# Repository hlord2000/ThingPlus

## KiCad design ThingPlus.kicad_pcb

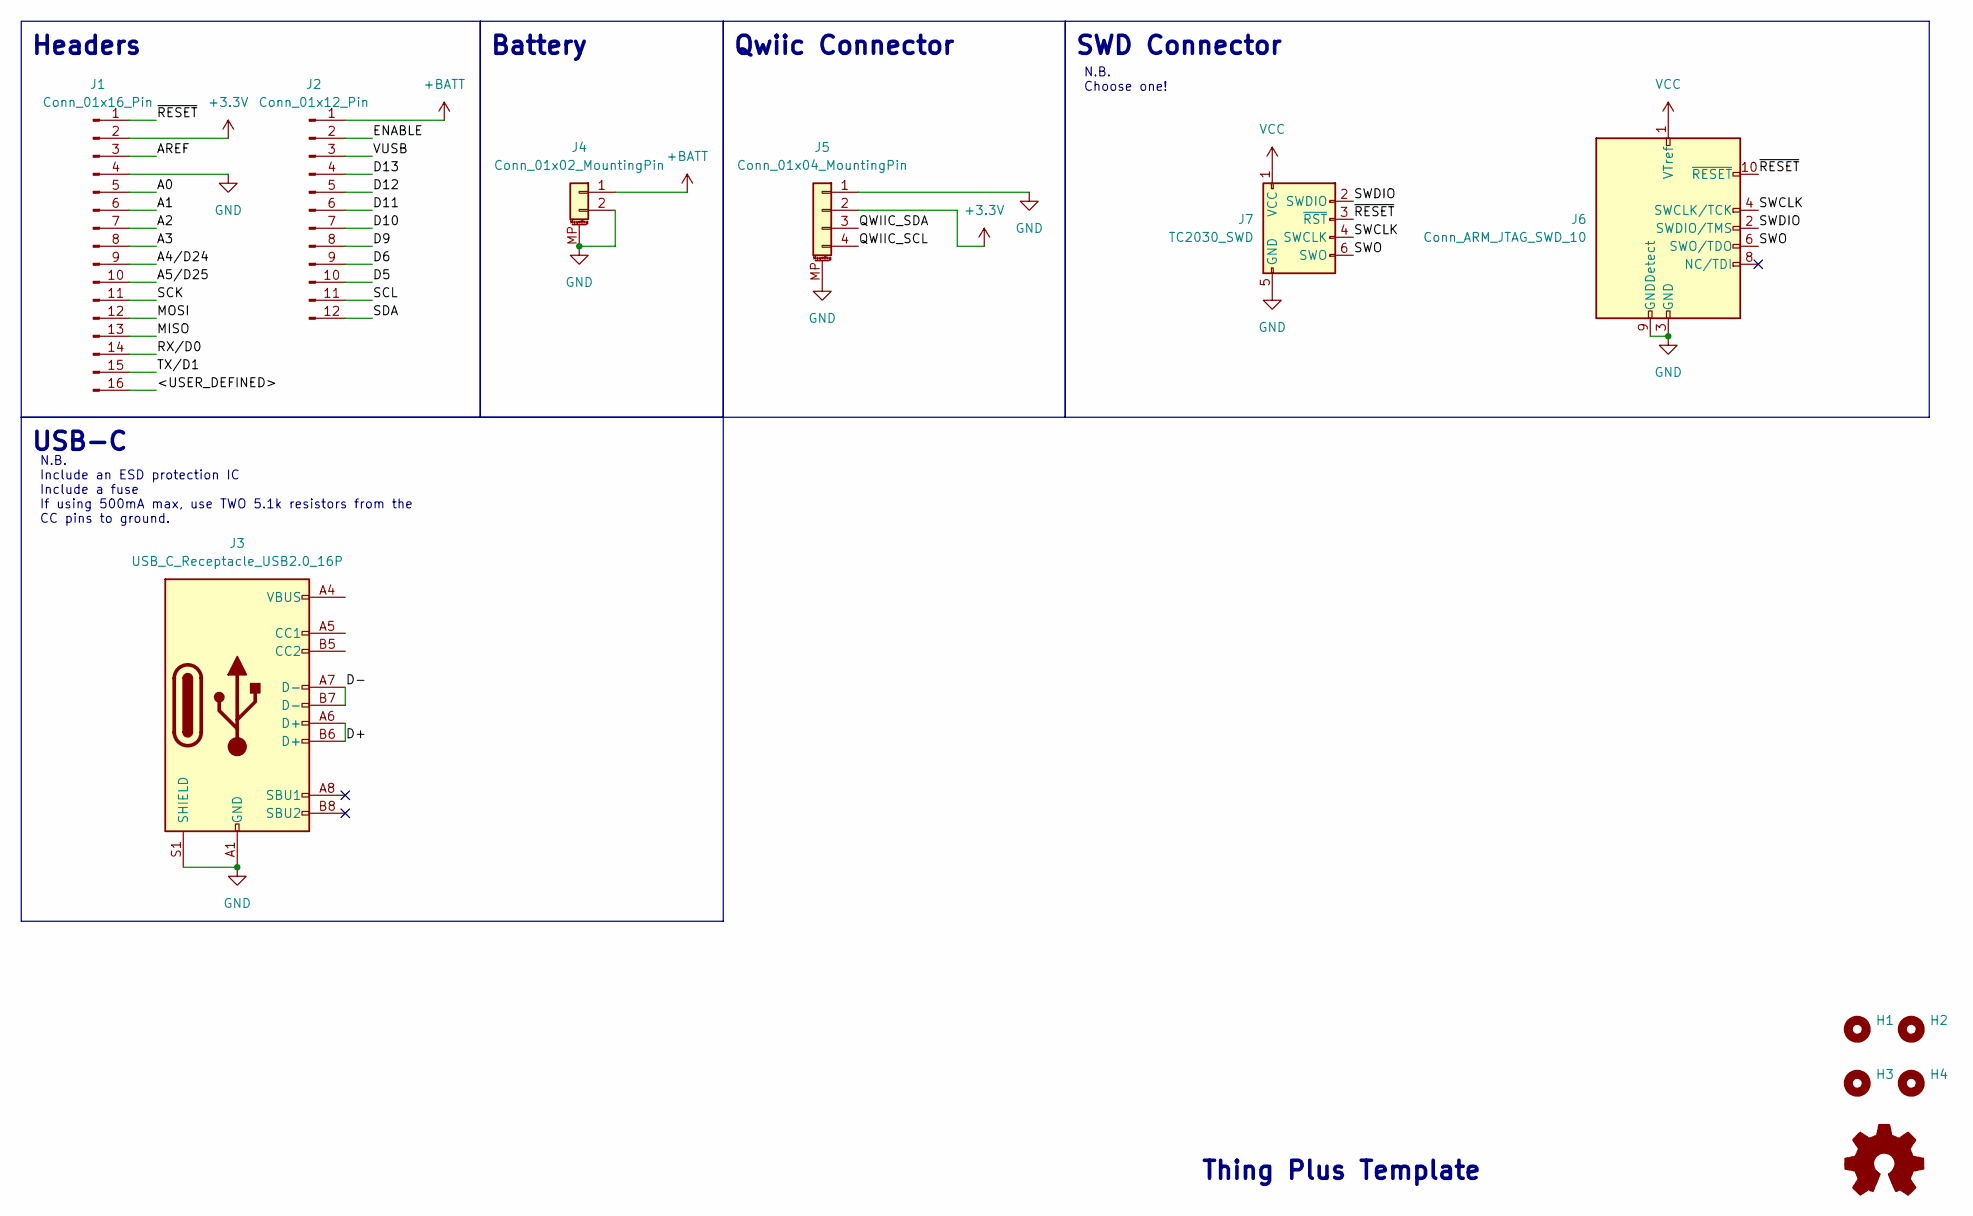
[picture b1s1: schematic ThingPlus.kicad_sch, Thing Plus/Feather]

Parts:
H1, H2, H3, H4: MountingHole; MountingHole_2.5mm
J1: Conn_01x16_Pin; PinHeader_1x16_P2.54mm_Vertical
J2: Conn_01x12_Pin; PinHeader_1x12_P2.54mm_Vertical
J3: USB_C_Receptacle_USB2.0_16P; USB_C_Receptacle_HRO_TYPE-C-31-M-12
J4: Conn_01x02_MountingPin; JST_PH_S2B-PH-SM4-TB_1x02-1MP_P2.00mm_Horizontal
J5: Conn_01x04_MountingPin; JST_SH_SM04B-SRSS-TB_1x04-1MP_P1.00mm_Horizontal
J6: Conn_ARM_JTAG_SWD_10; PinHeader_2x05_P1.27mm_Vertical_SMD
J7: TC2030_SWD; CON_TC2030_outlined

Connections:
+3.3V: J1.2, J5.2
+BATT: J2.1, J4.1
/<USER_DEFINED>: J1.16
/A0: J1.5
/A1: J1.6
/A2: J1.7
/A3: J1.8
/A4/D24: J1.9
/A5/D25: J1.10
/AREF: J1.3
/D5: J2.10
/D6: J2.9
/D9: J2.8
/D10: J2.7
/D11: J2.6
/D12: J2.5
/D13: J2.4
/D+: J3.A6 (D+), J3.B6 (D+)
/D-: J3.A7 (D-), J3.B7 (D-)
/ENABLE: J2.2
/MISO: J1.13
/MOSI: J1.12
/QWIIC_SCL: J5.4
/QWIIC_SDA: J5.3
/RX/D0: J1.14
/SCK: J1.11
/SCL: J2.11
/SDA: J2.12
/SWCLK: J6.4 (SWCLK/TCK), J7.4 (SWCLK)
/SWDIO: J6.2 (SWDIO/TMS), J7.2 (SWDIO)
/SWO: J6.6 (SWO/TDO), J7.6 (SWO)
/TX/D1: J1.15
/VUSB: J2.3
/~RESET: J1.1, J6.10 (~RESET), J7.3 (~RST)
GND: J1.4, J3.A1 (GND), J3.A12 (GND), J3.B1 (GND), J3.B12 (GND), J3.S1 (SHIELD), J4.2, J4.MP (MountPin), J5.1, J5.MP (MountPin), J6.3 (GND), J6.5 (GND), J6.9 (GNDDetect), J7.5 (GND)
unnamed: J3.A4 (VBUS), J3.A9 (VBUS), J3.B4 (VBUS), J3.B9 (VBUS)
VCC: J6.1 (VTref), J7.1 (VCC)

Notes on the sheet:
N.B. Include an ESD protection IC Include a fuse If using 500mA max, use TWO 5.1k resistors from the CC pins to ground.
SWD Connector
Headers
Qwiic Connector
USB-C
Thing Plus Template
Battery
N.B. Choose one!

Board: 2 copper layers, 11 parts (2 on the bottom side), 11 nets, no tracks yet.

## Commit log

2024-02-21 Updated README and added photos
